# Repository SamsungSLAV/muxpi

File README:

#####
MuxPi
#####

**MuxPi** is an open hardware and open software board which was designed to
aid in automating tasks on physical devices. Initial goal was to automate
testing on hardware platform, thus connected devices will be called **D**\evice
**U**\nder **T**\est or shortly **DUT**\.  Muxpi is intended to help in testing
of embedded systems, automatic software installation or flashing and automation
during development. MuxPi is connected between the DUT and a PC/Server machine
which will be managing the work.  The name of the board is based on its two
main components: **SD Mux** and **NanoPi**

********
Features
********

* Providing a DUT connection (UART, USB, ETH, microSD card) to remote location
  over Ethernet
* Switching a microSD card between a DUT's microSD card slot and an onboard
  USB card reader
* Flashing a microSD card using an onboard USB card reader
* Flashing and controlling state of Samsung mobile devices over fully
  controllable, dedicated USB interface
* Switching DUT's power supply
* Switching jumpers/buttons of a DUT in order to (re)boot/(re)configure it
* Measuring power consumption of a DUT
* Handling serial connection (UART) of a DUT
* Writing EDID to a DUT over HDMI connection
* Interacting with a user/maintainer over a simple, bidirectional interface

*************
Documentation
*************

`Muxpi documentation`_ is hosted on Read The Docs pages.

.. _`Muxpi documentation`: https://muxpi.rtfd.io/

******************************
Repository Directory structure
******************************

::

  .
  │
  └── doc - overall documentation for all of the components of MuxPi
  │
  └── hw - MuxPi board design and fabrication files
  │
  └── sw - MuxPi's software
      │
      └── attiny - firmware for ATtiny10 microcontroller (watchdog)
      │
      └── cortex - firmware for STM32F030 (controller)
      │
      └── nanopi - configs, scripts, tools, OS recipes, etc. for NanoPi NEO
          │
          └── config - ansible files for configuring NanoPi NEO
          │
          └── fota - tools/libs for flashing devices (usually microSD card)
          │   with given images
          │
          └── stm - tools/libs for communicating with STM32F030 microntroller
          │
          └── power - tool for controling power supply for  MuxPi's main board
          │
          └── gpio - tool for controling MuxPi's GPIOs including two one-color
          │   LEDs
          │
          └── firmware - tool for updating firmware of STM32 microntroller
          │
          └── nv - tool for writing and reading non-volatile data of MuxPi
          │
          └── debian - files for creating packages for Debian-based
              distributions

*******
License
*******

MuxPi is distributed under `Apache 2.0 License`_

.. _`Apache 2.0 License`: LICENSE

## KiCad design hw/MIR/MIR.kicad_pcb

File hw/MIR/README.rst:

#########
MIR addon
#########

This folder contains hardware documentation for MIR addon.
The documentation was created with KiCad nightly build.

For more information go to muxpi/sw/MuxPi-addons/MIR

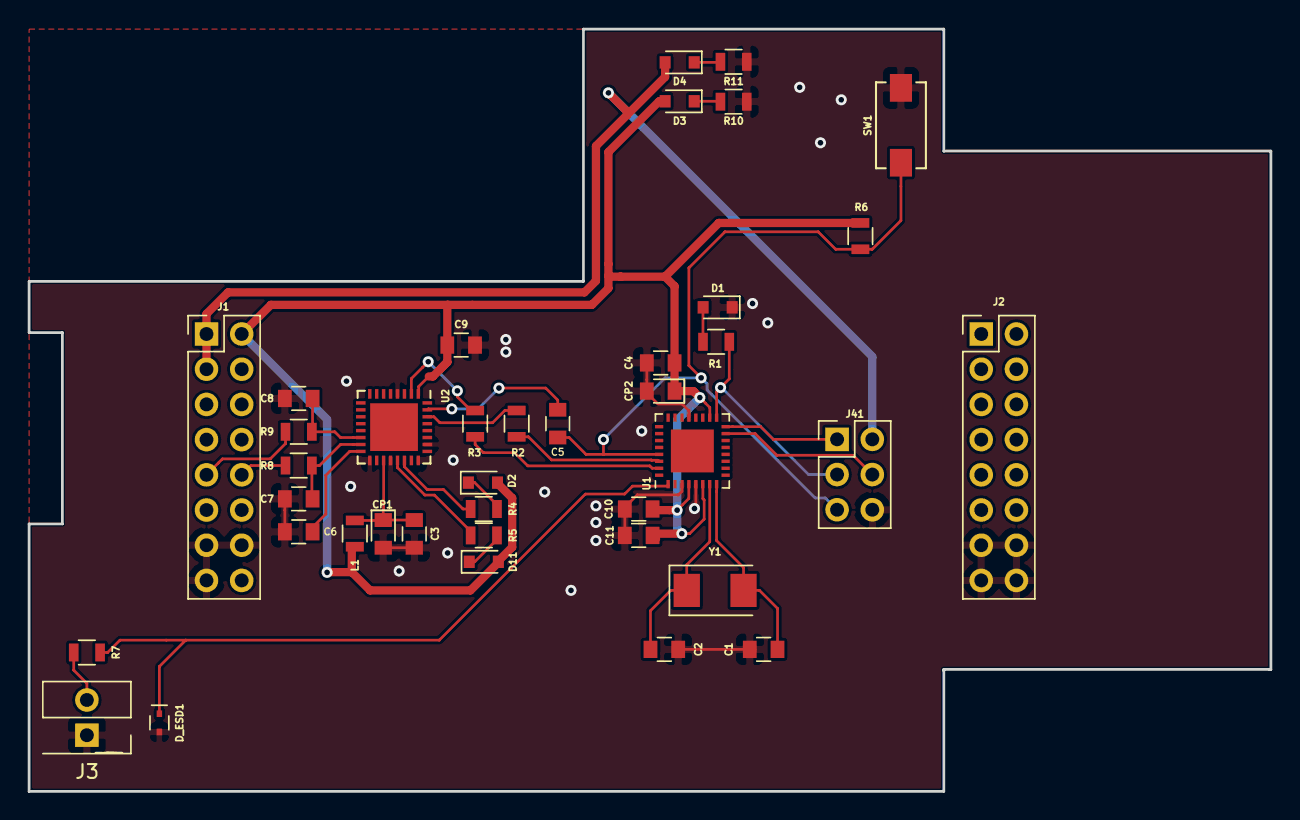
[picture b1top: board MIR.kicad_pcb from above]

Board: 2 copper layers, 89.6 x 55.0 mm, 40 parts (0 on the bottom side), 29 nets.

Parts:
C1, C2: 18pF; C_0805
C3, C4, C5, C6, C9, C10, C11: 0.1uF; C_0805
C7, C8: 47pF; C_0805
CP1, CP2: 4.7uF; C_T_0805
D1, D2, D3: KPT-2012SGC; D_0805
D4, D11: KPT-2012EC; D_0805
D5: LED_IR; EXTERNAL ELEMENT
D_ESD1: ESD5B5.0S; SOD-523
J1, J2: CONN_02X08; Pin_Header_Straight_2x08_Pitch2.54mm
J3: CONN_01X02; Pin_Header_Straight_1x02_Pitch2.54mm_Molex_022232021
J41: CONN_02X03; Pin_Header_Straight_2x03_Pitch2.54mm
L1: BLM21PG221SN1D; R_0805
R1, R4, R5, R7, R10, R11: 330R; R_0805
R2, R3: 1k; R_0805
R6: 1k1; R_0805
R8, R9: 27R; R_0805
SW1: SwitchPush; DTSM-3
U1: ATmega328P-MU; WQFN-32-1EP_5x5mm_Pitch0.5mm
U2: FT232RQ; QFN-32-1EP_5x5mm_Pitch0.5mm
Y1: 16MHz; Crystal_SMD_Abracon_ABM3-2pin_5.0x3.2mm_HandSoldering

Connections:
+5V: D4.2, J1.1, J1.3, J41.2
/D0-RX: R2.2, U1.30
/D1-TX: R3.2, U1.31
/D3: D_ESD1.1, R7.2, U1.1
/D11-MOSI: J41.4, U1.15
/D12-MISO: J41.1, U1.16
/D13-SCK: J41.3, R1.1, U1.17
/FT_VCC: C3.1, CP1.1, L1.1, U2.19
/RESET: C5.2, J41.5, R6.2, SW1.2, U1.29
/RX: R2.1, U2.30
/TX: R3.1, U2.2
/USB_B+: J1.9, R9.1
/USB_B-: J1.10, R8.1
GND: C1.2, C2.2, C3.2, C4.2, C6.1, C7.2, C8.1, C9.2, C10.2, C11.2, CP1.2, CP2.2, D1.1, D_ESD1.2, J1.13, J1.14, J1.15, J2.13, J2.14, J2.15, J2.16, J3.1, J41.6, R10.1, R11.1, SW1.1, U1.3, U1.5, U1.21, U2.4, U2.17, U2.20, U2.24, U2.26
unnamed: C1.1, U1.8, Y1.2
unnamed: C2.1, U1.7, Y1.1
unnamed: C5.1, U2.31
unnamed: C6.2, U2.16
unnamed: C7.1, R8.2, U2.15
unnamed: C8.2, R9.2, U2.14
unnamed: D1.2, R1.2
unnamed: D2.1, R4.2
unnamed: D3.1, R10.2
unnamed: D4.1, R11.2
unnamed: D11.1, R5.2
unnamed: J3.2, R7.1
unnamed: R4.1, U2.22
unnamed: R5.1, U2.21
VDD: C4.1, C9.1, C10.1, C11.1, CP2.1, D2.2, D3.2, D11.2, J1.2, L1.2, R6.1, U1.4, U1.6, U1.18, U2.1

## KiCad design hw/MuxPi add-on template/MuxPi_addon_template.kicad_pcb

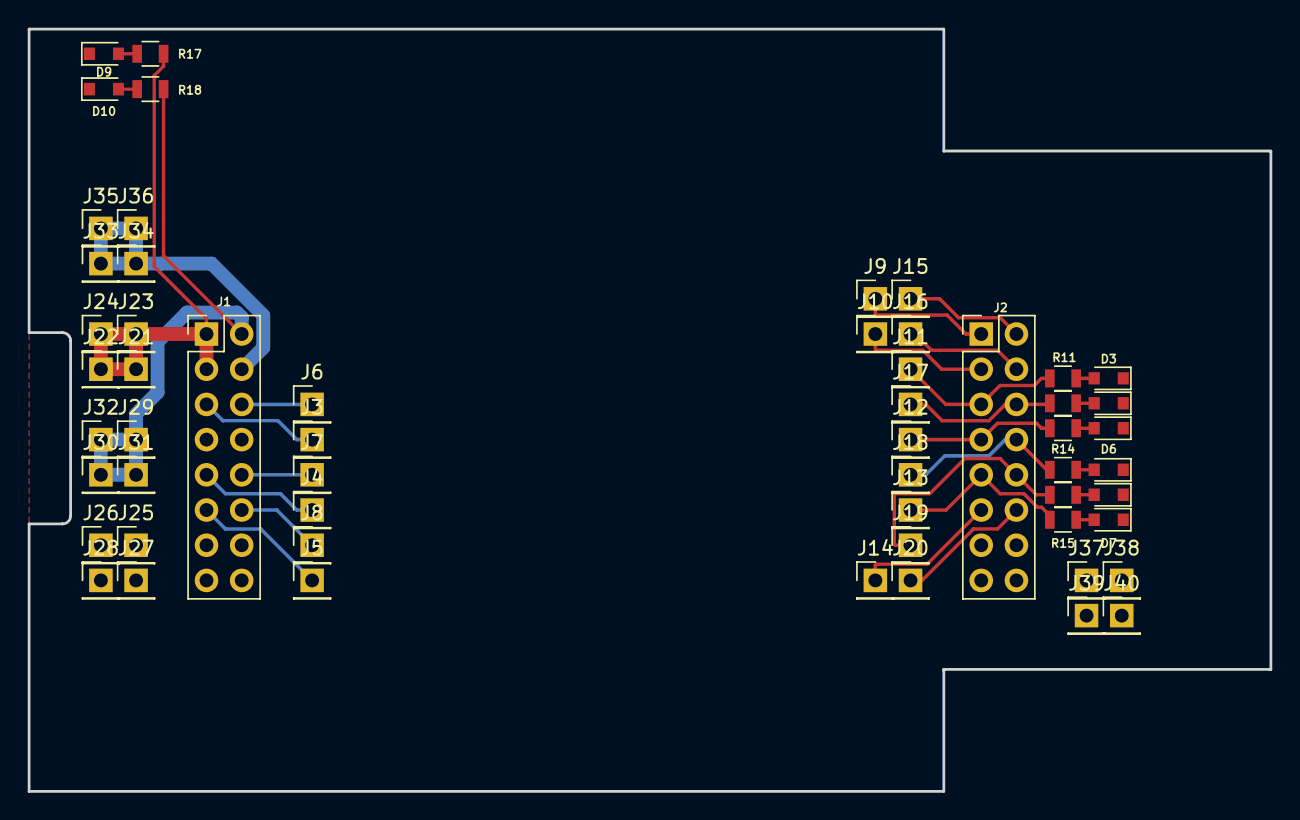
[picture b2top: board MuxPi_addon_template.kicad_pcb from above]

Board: 2 copper layers, 89.6 x 55.0 mm, 56 parts (0 on the bottom side), 30 nets.

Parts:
D3, D6, D9: KPT-2012EC; D_0805
D4, D7, D10: KPT-2012SGC; D_0805
D5, D8: OSB50805C1E; D_0805
J1, J2: CONN_02X08; Pin_Header_Straight_2x08_Pitch2.54mm
J3, J4, J5, J6, J7, J8, J9, J10, J11, J12, J13, J14, J15, J16, J17, J18, J19, J20, J21, J22, J23, J24, J25, J26, J27, J28, J29, J30, J31, J32, J33, J34, J35, J36, J37, J38, J39, J40: CONN_01X01; Pin_Header_Straight_1x01_Pitch2.54mm
R11, R12, R13, R14, R15, R16, R17, R18: 330R; R_0805

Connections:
+3V3: J1.4, J33.1, J34.1, J35.1, J36.1
+5V: J1.1, J1.3, J21.1, J22.1, J23.1, J24.1, R17.1
/ADC1: J2.11, J14.1
/ADC2: J2.12, J20.1
/PI_GPIO_1: J2.5, J11.1, R11.1
/PI_GPIO_2: J2.6, J17.1, R12.1
/PI_GPIO_3: J2.7, J12.1, R13.1
/SCL: J1.6, J6.1
/SDA: J1.5, J3.1
/SPI_CLK: J2.1, J9.1
/SPI_CS: J2.3, J10.1
/SPI_MISO: J2.4, J16.1
/SPI_MOSI: J2.2, J15.1
/ST_GPIO_1: J2.8, J18.1, R14.1
/ST_GPIO_2: J2.9, J13.1, R15.1
/ST_GPIO_3: J2.10, J19.1, R16.1
/USB_A+: J1.11, J5.1
/USB_A-: J1.12, J8.1
/USB_B+: J1.9, J4.1
/USB_B-: J1.10, J7.1
GND: D3.1, D4.1, D5.1, D6.1, D7.1, D8.1, D9.1, D10.1, J1.13, J1.14, J1.15, J2.13, J2.14, J2.15, J2.16, J25.1, J26.1, J27.1, J28.1, J37.1, J38.1, J39.1, J40.1
unnamed: D3.2, R11.2
unnamed: D4.2, R12.2
unnamed: D5.2, R13.2
unnamed: D6.2, R14.2
unnamed: D7.2, R15.2
unnamed: D8.2, R16.2
unnamed: D9.2, R17.2
unnamed: D10.2, R18.2
VDD: J1.2, J29.1, J30.1, J31.1, J32.1, R18.1

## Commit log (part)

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2018-11-27 Create patch set 4
    Uploaded patch set 4.
    Patch-set: 4
    Subject: Rename stm to muxpictl
    Commit: b9ec344b1583c97baf15cf1d026e6d6f1aa15db5
    Tag: autogenerated:gerrit:newPatchSet
    Groups: 879cb7d6c303ac005c0e9c7e5f3527b1ea281f7e
2018-11-27 Update patch set 4
    Patch Set 4: Verified-1
    Build Failed
    http://106.120.51.26:8080/job/slav-gerrithub-pipeline/60/ : FAILURE
    null
    Patch-set: 4
    Tag: autogenerated:jenkins-gerrit-trigger
2018-11-29 Update patch set 4
    Patch Set 4:
    (1 comment)
    Patch-set: 4
    Reviewer: Adam Malinowski <1015240@d5d70762-12d0-45a1-890d-524b12d3f735>
2018-11-29 Update patch set 1
    Patch Set 1: Code-Review+1
    Patch-set: 1
    Reviewer: Adam Malinowski <1015240@d5d70762-12d0-45a1-890d-524b12d3f735>
    Label: Code-Review=+1
2018-11-29 Add Docker building for Debian packages
    Running `make` in sw/nanopi/debian-auto directory should result in
    packages for armhf and amd64 being built using Docker into
    sw/nanopi/bin.
2018-11-29 Update unified Dockerfile
    Package versions were increased to match last released, same for
    PlantUML.
2018-11-30 Update patch set 1
    Patch Set 1: Code-Review-1
    (2 comments)
    Add please some reference to the library you use if it cannot be put here directly.
    Consider dropping arduino studio dependency by changing ino file to C and creating some simple Makefile.
    Patch-set: 1
    Reviewer: Adam Malinowski <1015240@d5d70762-12d0-45a1-890d-524b12d3f735>
2018-12-03 Update patch set 1
    Patch Set 1:
    (1 comment)
    Patch-set: 1
    CC: Alexander Mazuruk <1015231@d5d70762-12d0-45a1-890d-524b12d3f735>
2018-12-04 Add scripts to flash MIR
    I copied avrdude binary from Arduino IDE installation.
    To use it avrdude.conf is needed.
    flash.sh may be used to upload program onto MIR's Atmega.
2018-12-04 Create patch set 2
    Uploaded patch set 2.
    Patch-set: 2
    Subject: Add demo scennarios and remote rawcodes
    Commit: 9b2a39c99d483f5d12255d5585dd2b8299ea7073
    Tag: autogenerated:gerrit:newPatchSet
    Groups: 5082bff694d4c272037655d1c72b00dbf9292e4e
2018-12-04 Update patch set 2
    Patch Set 2:
    Build Started http://106.120.51.26:8080/job/slav-gerrithub-pipeline/75/
    Patch-set: 2
    Tag: autogenerated:jenkins-gerrit-trigger
    CC: bbotslav@gmail.com <1015489@d5d70762-12d0-45a1-890d-524b12d3f735>
2018-12-06 Create patch set 6
    Uploaded patch set 6.
    Patch-set: 6
    Subject: Various fixes in schematics and PCB design
    Commit: e8a7d1e493c82661898243b181d004e501d9c4f5
    Tag: autogenerated:gerrit:newPatchSet
    Groups: 5082bff694d4c272037655d1c72b00dbf9292e4e
2018-12-06 Update patch set 7
    Patch Set 7: Verified-1
    Build Failed
    http://106.120.51.26:8080/job/slav-gerrithub-pipeline/78/ : FAILURE <<<
    downloading patchset or dependencies failed...
    >>>
    null
2018-12-09 Update patch set 1
    Abandoned
    Patch-set: 1
    Status: abandoned
    Tag: autogenerated:gerrit:abandon
2018-12-09 Update patch set 1
    Patch Set 1:
    Moved commit up- now renames this funciton in both sflasher and muxpictl.
    Patch-set: 1
    Reviewer: Alexander Mazuruk <1015231@d5d70762-12d0-45a1-890d-524b12d3f735>
2018-12-09 Change log to slav/logger in muxpictl package
    * Add more logs
    Dummy mode:
    * Every action is logged as Notice (default log level).
    * Removed prefixing from dummy (SLAV logger does it by default).
    TODO: add logs to current measurement functions.
2018-12-09 Create patch set 2
    Uploaded patch set 2.
    Patch-set: 2
    Subject: Rename checkErr func to exitOnErr
    Commit: 9d7ec9dc4bb516ef135cb75f128cf2c3d1095cf0
    Tag: autogenerated:gerrit:newPatchSet
    Groups: 879cb7d6c303ac005c0e9c7e5f3527b1ea281f7e
2018-12-09 Update patch set 2
    Patch Set 2:
    Build Started http://106.120.51.26:8080/job/slav-gerrithub-pipeline/95/
    Patch-set: 2
    Tag: autogenerated:jenkins-gerrit-trigger
    CC: bbotslav@gmail.com <1015489@d5d70762-12d0-45a1-890d-524b12d3f735>
2019-01-11 Update patch set 3
    Patch Set 3: Code-Review-1
    (1 comment)
    Patch-set: 3
    Reviewer: Gerrit User 1015240 <1015240@d5d70762-12d0-45a1-890d-524b12d3f735>
    Label: Code-Review=-1
2019-01-16 Create patch set 3
    Uploaded patch set 3: Patch Set 2 was rebased.
    Patch-set: 3
    Subject: [Obsolete] Add footprints and pcb
    Commit: eb6de1907c2b241b3a278450d9ef2908fecf0ef1
    Tag: autogenerated:gerrit:newPatchSet
    Groups: b8fbb05ee0338093f1d00c442b0d55f97eaf27b4
2019-01-16 Update patch set 4
    Patch Set 4:
    Build Started http://106.120.51.26:8080/job/slav-gerrithub-pipeline/187/
    Patch-set: 4
    Tag: autogenerated:jenkins-gerrit-trigger
    Reviewer: Gerrit User 1015489 <1015489@d5d70762-12d0-45a1-890d-524b12d3f735>
2019-01-16 Create patch set 11
    Uploaded patch set 11: Patch Set 10 was rebased.
    Patch-set: 11
    Subject: Various fixes in schematics and PCB design
    Commit: 2172d766bd0e8036693aec1280fb3129825a841f
    Tag: autogenerated:gerrit:newPatchSet
    Groups: b8fbb05ee0338093f1d00c442b0d55f97eaf27b4
2019-01-16 Update patch set 5
    Patch Set 5: Verified+1 Code-Review+2
    Patch-set: 5
    Reviewer: Gerrit User 1015240 <1015240@d5d70762-12d0-45a1-890d-524b12d3f735>
    Label: Code-Review=+2
    Label: Verified=+1
2019-01-16 Update patch set 3
    Change has been successfully merged by Adam Malinowski
    Patch-set: 3
    Status: merged
    Tag: autogenerated:gerrit:merged
    Reviewer: Gerrit User 1015240 <1015240@d5d70762-12d0-45a1-890d-524b12d3f735>
    Label: SUBM=+1
2019-01-16 Update notes for submitted changes
    * Add module for translating codes from hex to raw format
2019-01-17 Create change
    Uploaded patch set 1.
    Patch-set: 1
    Subject: Add simple README files to IR addon
    Branch: refs/heads/master
    Status: new
    Topic:
2019-01-18 Update patch set 2
    Patch Set 2:
    Build Started http://106.120.51.26:8080/job/slav-gerrithub-pipeline/190/
    Patch-set: 2
    Tag: autogenerated:jenkins-gerrit-trigger
    Reviewer: Gerrit User 1015489 <1015489@d5d70762-12d0-45a1-890d-524b12d3f735>
2019-01-18 Create patch set 3
    Uploaded patch set 3.
    Patch-set: 3
    Subject: Add simple README files to IR addon
    Commit: d1b0600f461af9f283f0401f429d4a47c68705fa
    Tag: autogenerated:gerrit:newPatchSet
    Groups: c4734bd08595009428653480f5d1314f3c1c72f8
2019-01-18 Update patch set 4
    Patch Set 4:
    Build Started http://106.120.51.26:8080/job/slav-gerrithub-pipeline/193/
    Patch-set: 4
    Tag: autogenerated:jenkins-gerrit-trigger
    Reviewer: Gerrit User 1015489 <1015489@d5d70762-12d0-45a1-890d-524b12d3f735>
2019-01-21 Create patch set 6
    Uploaded patch set 6.
    Patch-set: 6
    Subject: Add simple README files to MIR addon
    Commit: 3b8b84d19a27acfcc63bd1cc2a4b417faa00d7d0
    Tag: autogenerated:gerrit:newPatchSet
    Groups: 5368b7c1e410017282381822b9fadac64b1b8e5c
2019-01-21 Create patch set 7
    Uploaded patch set 7.
    Patch-set: 7
    Subject: Add simple README files to MIR addon
    Commit: a37d0fd59f0a71847397647cdc0bbd910ea89904
    Tag: autogenerated:gerrit:newPatchSet
    Groups: 5368b7c1e410017282381822b9fadac64b1b8e5c
2019-01-21 Update patch set 7
    Patch Set 7: Verified+1 Code-Review+2
    Patch-set: 7
    Reviewer: Gerrit User 1015240 <1015240@d5d70762-12d0-45a1-890d-524b12d3f735>
    Label: Code-Review=+2
    Label: Verified=+1
2019-01-21 Create patch set 6
    Uploaded patch set 6: Patch Set 5 was rebased.
    Patch-set: 6
    Subject: Rename fota to sflasher
    Commit: 36c79a27e889e5c82b2d7a7c65b36bb52ad9c3c9
    Tag: autogenerated:gerrit:newPatchSet
    Groups: c826c46e52df0b8fc743eeaba8e8d0b0e2e3452f
2019-01-21 Create patch set 3
    Uploaded patch set 3: Patch Set 2 was rebased.
    Patch-set: 3
    Subject: Change log to slav/logger in muxpictl package
    Commit: e91732d6445c6952072595890690537036f6a9b7
    Tag: autogenerated:gerrit:newPatchSet
    Groups: c826c46e52df0b8fc743eeaba8e8d0b0e2e3452f
2019-01-22 Create change
    Uploaded patch set 1.
    Patch-set: 1
    Subject: Sflasher stops checking for SD card avaliability.
    Branch: refs/heads/master
    Status: new
    Topic:
2019-01-22 Create change
    Uploaded patch set 1.
    Patch-set: 1
    Subject: Add mapping example in sflasher
    Branch: refs/heads/logger
    Status: new
    Topic:
2019-01-22 Update patch set 5
    Patch Set 5:
    Build Started http://106.120.51.26:8080/job/slav-gerrithub-pipeline/199/
    Patch-set: 5
    Tag: autogenerated:jenkins-gerrit-trigger
    Reviewer: Gerrit User 1015489 <1015489@d5d70762-12d0-45a1-890d-524b12d3f735>
2019-01-22 Update patch set 1
    Patch Set 1:
    Build Started http://106.120.51.26:8080/job/slav-gerrithub-pipeline/202/
    Patch-set: 1
    Tag: autogenerated:jenkins-gerrit-trigger
    CC: Gerrit User 1015489 <1015489@d5d70762-12d0-45a1-890d-524b12d3f735>
2019-01-22 Create patch set 3
    Uploaded patch set 3: Patch Set 2 was rebased.
    Patch-set: 3
    Subject: Add mapping example in sflasher
    Commit: 0cefd1917b211ca2256be20c58ddb50549172d39
    Tag: autogenerated:gerrit:newPatchSet
    Groups: c826c46e52df0b8fc743eeaba8e8d0b0e2e3452f
2019-01-22 Create patch set 5
    Uploaded patch set 5: New patch set was added with same tree, parent, and commit message as Patch Set 4.
    Patch-set: 5
    Subject: Rename checkErr func to exitOnErr
    Commit: 1b43ca053b9ddad87d0882054fc12883fd223454
    Tag: autogenerated:gerrit:newPatchSet
    Groups: c826c46e52df0b8fc743eeaba8e8d0b0e2e3452f
2019-01-22 Update patch set 6
    Patch Set 6: Verified-1
    Build Failed
    http://106.120.51.26:8080/job/slav-gerrithub-pipeline/206/ : FAILURE <<<
    tests failed...
    >>>
    null
2019-01-22 Update patch set 5
    Patch Set 5: Verified-1
    Build Failed
    http://106.120.51.26:8080/job/slav-gerrithub-pipeline/209/ : FAILURE <<<
    tests failed...
    >>>
    null
2019-01-24 Update patch set 7
    Patch Set 7:
    (1 comment)
    Patch-set: 7
    Reviewer: Gerrit User 1015231 <1015231@d5d70762-12d0-45a1-890d-524b12d3f735>
2019-01-24 Update patch set 6
    Patch Set 6: Code-Review-1
    (6 comments)
    Patch-set: 6
    Reviewer: Gerrit User 1015240 <1015240@d5d70762-12d0-45a1-890d-524b12d3f735>
    Label: Code-Review=-1
2019-01-24 Create patch set 3
    Uploaded patch set 3.
    Patch-set: 3
    Subject: Stop sflasher from switching SD card
    Commit: 9abc6da7864a69e2bffd0876dd97bfb4dc7b5dd1
    Tag: autogenerated:gerrit:newPatchSet
    Groups: e8a13b8643262e539c6d74909e0afb03fda08842
2019-01-24 Update patch set 7
    Patch-set: 7
    Reviewer: Gerrit User 1015210 <1015210@d5d70762-12d0-45a1-890d-524b12d3f735>
    Reviewer: Gerrit User 1015231 <1015231@d5d70762-12d0-45a1-890d-524b12d3f735>
2019-01-24 Update patch set 6
    Patch Set 6:
    (6 comments)
    Patch-set: 6
    Reviewer: Gerrit User 1015231 <1015231@d5d70762-12d0-45a1-890d-524b12d3f735>
2019-01-24 Update patch set 7
    Patch Set 7:
    Build Started http://106.120.51.26:8080/job/slav-gerrithub-pipeline/220/
    Patch-set: 7
    Tag: autogenerated:jenkins-gerrit-trigger
    Reviewer: Gerrit User 1015489 <1015489@d5d70762-12d0-45a1-890d-524b12d3f735>
2019-01-24 Update patch set 6
    Patch Set 6:
    Build Started http://106.120.51.26:8080/job/slav-gerrithub-pipeline/223/
    Patch-set: 6
    Tag: autogenerated:jenkins-gerrit-trigger
    Reviewer: Gerrit User 1015489 <1015489@d5d70762-12d0-45a1-890d-524b12d3f735>
2019-04-12 Silkscreen symbols update
2019-05-21 Update patch set 3
    Patch Set 3: Code-Review+2
    Patch-set: 3
    Reviewer: Gerrit User 1015240 <1015240@d5d70762-12d0-45a1-890d-524b12d3f735>
    Label: Code-Review=+2
2019-10-29 Create patch set 3
    Uploaded patch set 3.
    Patch-set: 3
    Subject: Add source code of STM32 firmware
    Commit: 0b560677d3db946b8e6c4784983b8b013e11646e
    Tag: autogenerated:gerrit:newPatchSet
    Groups: 0b560677d3db946b8e6c4784983b8b013e11646e
2019-10-29 Update notes for submitted changes
    * Add LICENSE file
2019-10-29 Update patch set 2
    Change has been successfully merged by Adam Malinowski
    Patch-set: 2
    Status: merged
    Tag: autogenerated:gerrit:merged
    Reviewer: Gerrit User 1015240 <1015240@d5d70762-12d0-45a1-890d-524b12d3f735>
    Label: SUBM=+1

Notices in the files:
hw/MIR/MIR.kicad_pcb:
Copyright (c) 2018 Samsung Electronics Co., Ltd All Rights Reserved
